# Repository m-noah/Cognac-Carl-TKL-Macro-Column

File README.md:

# Cognac-Carl-TKL-Macro-Column
 TKL with left hand macro column

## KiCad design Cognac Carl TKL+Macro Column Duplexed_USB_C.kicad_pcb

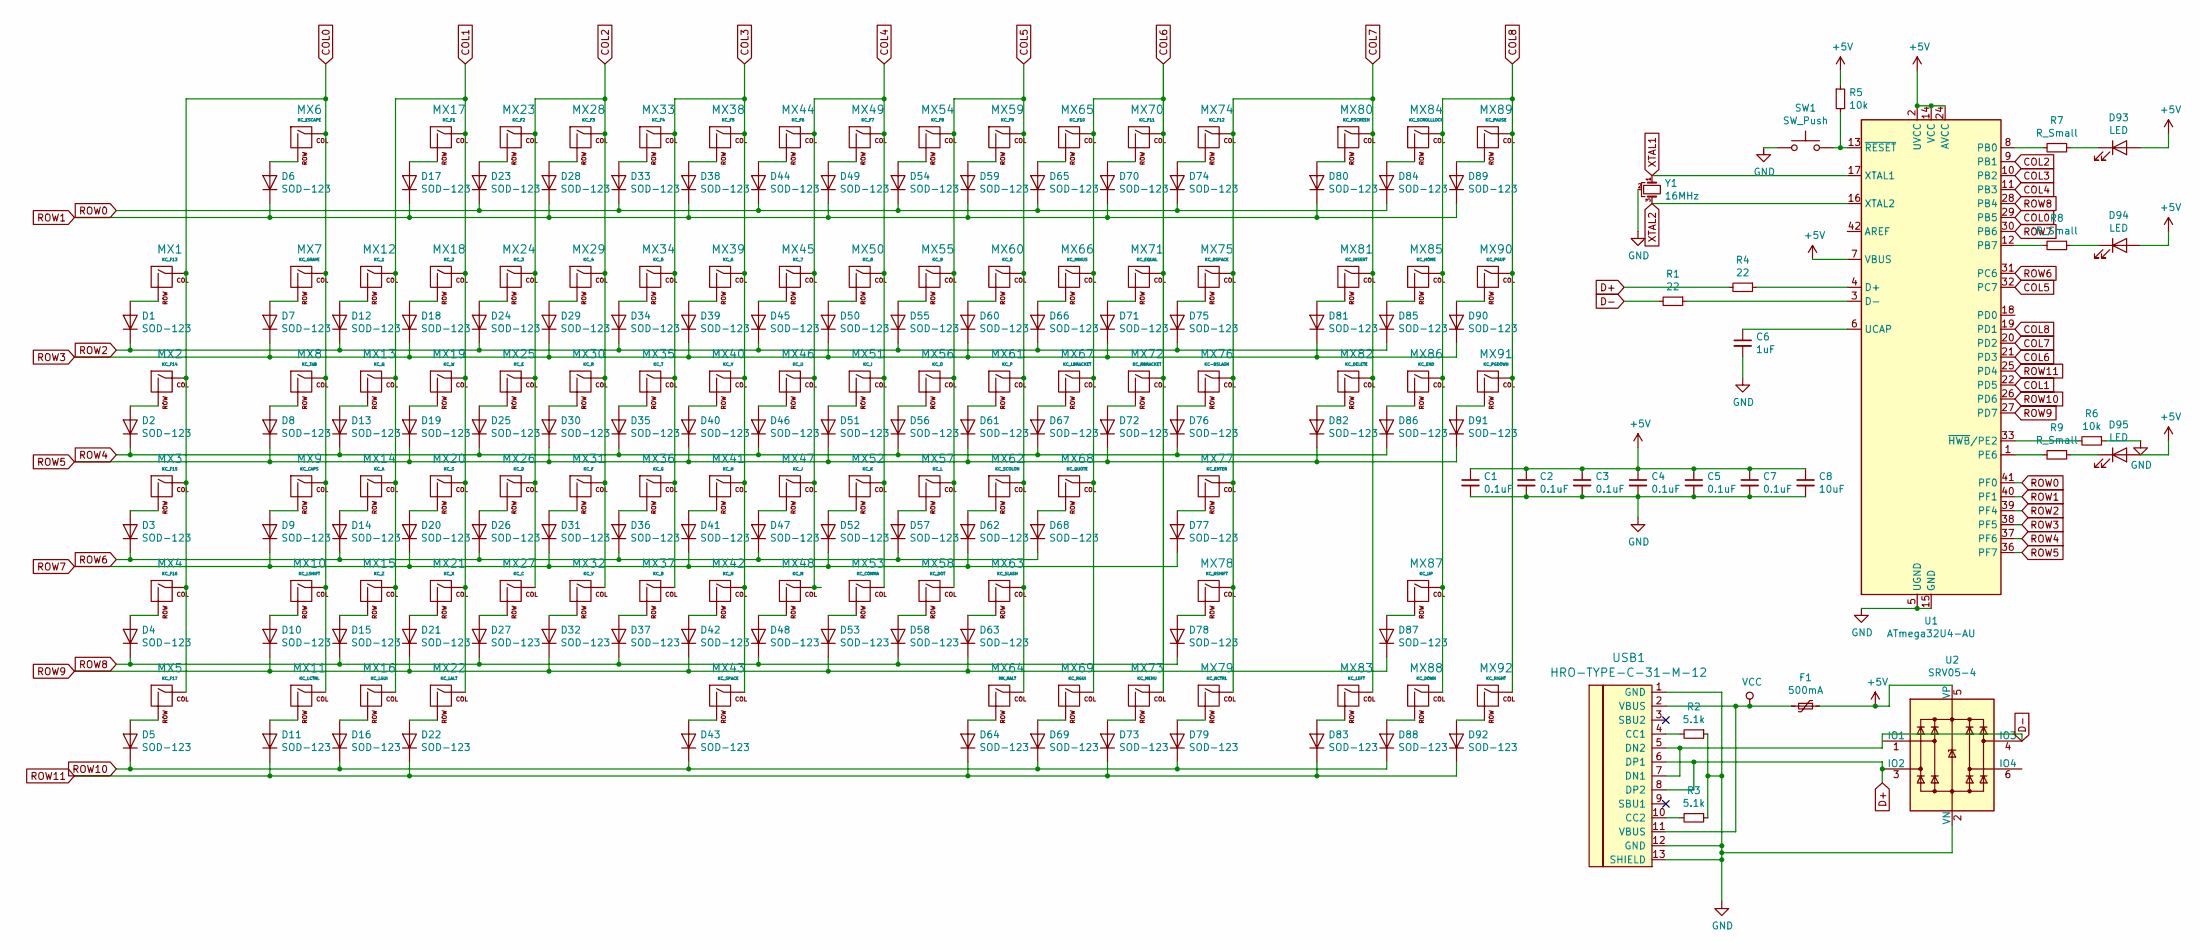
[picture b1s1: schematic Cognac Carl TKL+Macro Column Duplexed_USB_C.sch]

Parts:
C1, C2, C3, C4, C5, C7: 0.1uF; C_0805_2012Metric
C6: 1uF; C_0805_2012Metric
C8: 10uF; C_0805_2012Metric
D1, D2, D3, D4, D5, D6, D7, D8, D9, D10, D11, D12, D13, D14, D15, D16, D17, D18, D19, D20, D21, D22, D23, D24, D25, D26, D27, D28, D29, D30, D31, D32, D33, D34, D35, D36, D37, D38, D39, D40, D41, D42, D43, D44, D45, D46, D47, D48, D49, D50, D51, D52, D53, D54, D55, D56, D57, D58, D59, D60, D61, D62, D63, D64, D65, D66, D67, D68, D69, D70, D71, D72, D73, D74, D75, D76, D77, D78, D79, D80, D81, D82, D83, D84, D85, D86, D87, D88, D89, D90, D91, D92: SOD-123; D_SOD-123
D93, D94, D95: LED; LED_0805_2012Metric
F1: 500mA; Fuse_1206_3216Metric
MX1: KC_F13; MXOnly-1U-NoLED
MX2: KC_F14; MXOnly-1U-NoLED
MX3: KC_F15; MXOnly-1U-NoLED
MX4: KC_F16; MXOnly-1U-NoLED
MX5: KC_F17; MXOnly-1U-NoLED
MX6: KC_ESCAPE; MXOnly-1U-NoLED
MX7: KC_GRAVE; MXOnly-1U-NoLED
MX8: KC_TAB; MXOnly-1.5U-NoLED
MX9: KC_CAPS; MXOnly-1.75U-NoLED
MX10: KC_LSHIFT; MXOnly-2.25U-NoLED
MX11: KC_LCTRL; MXOnly-1.25U-NoLED
MX12: KC_1; MXOnly-1U-NoLED
MX13: KC_Q; MXOnly-1U-NoLED
MX14: KC_A; MXOnly-1U-NoLED
MX15: KC_Z; MXOnly-1U-NoLED
MX16: KC_LGUI; MXOnly-1.25U-NoLED
MX17: KC_F1; MXOnly-1U-NoLED
MX18: KC_2; MXOnly-1U-NoLED
MX19: KC_W; MXOnly-1U-NoLED
MX20: KC_S; MXOnly-1U-NoLED
MX21: KC_X; MXOnly-1U-NoLED
MX22: KC_LALT; MXOnly-1.25U-NoLED
MX23: KC_F2; MXOnly-1U-NoLED
MX24: KC_3; MXOnly-1U-NoLED
MX25: KC_E; MXOnly-1U-NoLED
MX26: KC_D; MXOnly-1U-NoLED
MX27: KC_C; MXOnly-1U-NoLED
MX28: KC_F3; MXOnly-1U-NoLED
MX29: KC_4; MXOnly-1U-NoLED
MX30: KC_R; MXOnly-1U-NoLED
MX31: KC_F; MXOnly-1U-NoLED
MX32: KC_V; MXOnly-1U-NoLED
MX33: KC_F4; MXOnly-1U-NoLED
MX34: KC_5; MXOnly-1U-NoLED
MX35: KC_T; MXOnly-1U-NoLED
MX36: KC_G; MXOnly-1U-NoLED
MX37: KC_B; MXOnly-1U-NoLED
MX38: KC_F5; MXOnly-1U-NoLED
MX39: KC_6; MXOnly-1U-NoLED
MX40: KC_Y; MXOnly-1U-NoLED
MX41: KC_H; MXOnly-1U-NoLED
MX42: KC_N; MXOnly-1U-NoLED
MX43: KC_SPACE; MXOnly-6.25U-ReversedStabilizers-NoLED
MX44: KC_F6; MXOnly-1U-NoLED
MX45: KC_7; MXOnly-1U-NoLED
MX46: KC_U; MXOnly-1U-NoLED
MX47: KC_J; MXOnly-1U-NoLED
MX48: KC_M; MXOnly-1U-NoLED
MX49: KC_F7; MXOnly-1U-NoLED
MX50: KC_8; MXOnly-1U-NoLED
MX51: KC_I; MXOnly-1U-NoLED
MX52: KC_K; MXOnly-1U-NoLED
MX53: KC_COMMA; MXOnly-1U-NoLED
MX54: KC_F8; MXOnly-1U-NoLED
MX55: KC_9; MXOnly-1U-NoLED
MX56: KC_O; MXOnly-1U-NoLED
MX57: KC_L; MXOnly-1U-NoLED
MX58: KC_DOT; MXOnly-1U-NoLED
MX59: KC_F9; MXOnly-1U-NoLED
MX60: KC_0; MXOnly-1U-NoLED
MX61: KC_P; MXOnly-1U-NoLED
MX62: KC_SCOLON; MXOnly-1U-NoLED
MX63: KC_SLASH; MXOnly-1U-NoLED
MX64: MX_RALT; MXOnly-1.25U-NoLED
MX65: KC_F10; MXOnly-1U-NoLED
MX66: KC_MINUS; MXOnly-1U-NoLED
MX67: KC_LBRACKET; MXOnly-1U-NoLED
MX68: KC_QUOTE; MXOnly-1U-NoLED
MX69: KC_RGUI; MXOnly-1.25U-NoLED
MX70: KC_F11; MXOnly-1U-NoLED
MX71: KC_EQUAL; MXOnly-1U-NoLED
MX72: KC_RBRACKET; MXOnly-1U-NoLED
MX73: KC_MENU; MXOnly-1.25U-NoLED
MX74: KC_F12; MXOnly-1U-NoLED
MX75: KC_BSPACE; MXOnly-2U-NoLED
MX76: KC-BSLASH; MXOnly-1.5U-NoLED
MX77: KC_ENTER; MXOnly-2.25U-ReversedStabilizers-NoLED
MX78: KC_RSHIFT; MXOnly-2.75U-NoLED
MX79: KC_RCTRL; MXOnly-1.25U-NoLED
MX80: KC_PSCREEN; MXOnly-1U-NoLED
MX81: KC_INSERT; MXOnly-1U-NoLED
MX82: KC_DELETE; MXOnly-1U-NoLED
MX83: KC_LEFT; MXOnly-1U-NoLED
MX84: KC_SCROLLLOCK; MXOnly-1U-NoLED
MX85: KC_HOME; MXOnly-1U-NoLED
MX86: KC_END; MXOnly-1U-NoLED
MX87: KC_UP; MXOnly-1U-NoLED
MX88: KC_DOWN; MXOnly-1U-NoLED
MX89: KC_PAUSE; MXOnly-1U-NoLED
MX90: KC_PGUP; MXOnly-1U-NoLED
MX91: KC_PGDOWN; MXOnly-1U-NoLED
MX92: KC_RIGHT; MXOnly-1U-NoLED
R1, R4: 22; R_0805_2012Metric
R2, R3: 5.1k; R_0805_2012Metric
R5, R6: 10k; R_0805_2012Metric
R7, R8, R9: R_Small; R_0805_2012Metric
SW1: SW_Push; SKQG-1155865
U1: ATmega32U4-AU; TQFP-44_10x10mm_P0.8mm
U2: SRV05-4; SOT-23-6
USB1: HRO-TYPE-C-31-M-12
Y1: 16MHz; Resonator_SMD_muRata_CSTxExxV-3Pin_3.0x1.1mm

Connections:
+5V: C1.1, C2.1, C3.1, C4.1, C5.1, C7.1, C8.1, D93.2 (A), D94.2 (A), D95.2 (A), F1.1, R5.1, U1.2 (UVCC), U1.7 (VBUS), U1.14 (VCC), U1.24 (AVCC), U1.34 (VCC), U1.44 (AVCC), U2.5 (VP)
COL0: MX1.1 (COL), MX2.1 (COL), MX3.1 (COL), MX4.1 (COL), MX5.1 (COL), MX6.1 (COL), MX7.1 (COL), MX8.1 (COL), MX9.1 (COL), MX10.1 (COL), MX11.1 (COL), U1.29 (PB5)
COL1: MX12.1 (COL), MX13.1 (COL), MX14.1 (COL), MX15.1 (COL), MX16.1 (COL), MX17.1 (COL), MX18.1 (COL), MX19.1 (COL), MX20.1 (COL), MX21.1 (COL), MX22.1 (COL), U1.22 (PD5)
COL2: MX23.1 (COL), MX24.1 (COL), MX25.1 (COL), MX26.1 (COL), MX27.1 (COL), MX28.1 (COL), MX29.1 (COL), MX30.1 (COL), MX31.1 (COL), MX32.1 (COL), U1.9 (PB1)
COL3: MX33.1 (COL), MX34.1 (COL), MX35.1 (COL), MX36.1 (COL), MX37.1 (COL), MX38.1 (COL), MX39.1 (COL), MX40.1 (COL), MX41.1 (COL), MX42.1 (COL), MX43.1 (COL), U1.10 (PB2)
COL4: MX44.1 (COL), MX45.1 (COL), MX46.1 (COL), MX47.1 (COL), MX48.1 (COL), MX49.1 (COL), MX50.1 (COL), MX51.1 (COL), MX52.1 (COL), MX53.1 (COL), U1.11 (PB3)
COL5: MX54.1 (COL), MX55.1 (COL), MX56.1 (COL), MX57.1 (COL), MX58.1 (COL), MX59.1 (COL), MX60.1 (COL), MX61.1 (COL), MX62.1 (COL), MX63.1 (COL), MX64.1 (COL), U1.32 (PC7)
COL6: MX65.1 (COL), MX66.1 (COL), MX67.1 (COL), MX68.1 (COL), MX69.1 (COL), MX70.1 (COL), MX71.1 (COL), MX72.1 (COL), MX73.1 (COL), U1.21 (PD3)
COL7: MX74.1 (COL), MX75.1 (COL), MX76.1 (COL), MX77.1 (COL), MX78.1 (COL), MX79.1 (COL), MX80.1 (COL), MX81.1 (COL), MX82.1 (COL), MX83.1 (COL), U1.20 (PD2)
COL8: MX84.1 (COL), MX85.1 (COL), MX86.1 (COL), MX87.1 (COL), MX88.1 (COL), MX89.1 (COL), MX90.1 (COL), MX91.1 (COL), MX92.1 (COL), U1.19 (PD1)
D+: R4.2, U2.3 (IO2), USB1.6 (DP1), USB1.8 (DP2)
D-: R1.2, U2.4 (IO3), USB1.5 (DN2), USB1.7 (DN1)
GND: C1.2, C2.2, C3.2, C4.2, C5.2, C6.2, C7.2, C8.2, R2.1, R3.1, R6.1, SW1.1, U1.5 (UGND), U1.15 (GND), U1.23 (GND), U1.35 (GND), U1.43 (GND), U2.2 (VN), USB1.1 (GND), USB1.12 (GND), USB1.13 (SHIELD), Y1.2
unnamed: C6.1, U1.6 (UCAP)
unnamed: D1.2 (A), MX1.2 (ROW)
unnamed: D2.2 (A), MX2.2 (ROW)
unnamed: D3.2 (A), MX3.2 (ROW)
unnamed: D4.2 (A), MX4.2 (ROW)
unnamed: D5.2 (A), MX5.2 (ROW)
unnamed: D6.2 (A), MX6.2 (ROW)
unnamed: D7.2 (A), MX7.2 (ROW)
unnamed: D8.2 (A), MX8.2 (ROW)
unnamed: D9.2 (A), MX9.2 (ROW)
unnamed: D10.2 (A), MX10.2 (ROW)
unnamed: D11.2 (A), MX11.2 (ROW)
unnamed: D12.2 (A), MX12.2 (ROW)
unnamed: D13.2 (A), MX13.2 (ROW)
unnamed: D14.2 (A), MX14.2 (ROW)
unnamed: D15.2 (A), MX15.2 (ROW)
unnamed: D16.2 (A), MX16.2 (ROW)
unnamed: D17.2 (A), MX17.2 (ROW)
unnamed: D18.2 (A), MX18.2 (ROW)
unnamed: D19.2 (A), MX19.2 (ROW)
unnamed: D20.2 (A), MX20.2 (ROW)
unnamed: D21.2 (A), MX21.2 (ROW)
unnamed: D22.2 (A), MX22.2 (ROW)
unnamed: D23.2 (A), MX23.2 (ROW)
unnamed: D24.2 (A), MX24.2 (ROW)
unnamed: D25.2 (A), MX25.2 (ROW)
unnamed: D26.2 (A), MX26.2 (ROW)
unnamed: D27.2 (A), MX27.2 (ROW)
unnamed: D28.2 (A), MX28.2 (ROW)
unnamed: D29.2 (A), MX29.2 (ROW)
unnamed: D30.2 (A), MX30.2 (ROW)
unnamed: D31.2 (A), MX31.2 (ROW)
unnamed: D32.2 (A), MX32.2 (ROW)
unnamed: D33.2 (A), MX33.2 (ROW)
unnamed: D34.2 (A), MX34.2 (ROW)
unnamed: D35.2 (A), MX35.2 (ROW)
unnamed: D36.2 (A), MX36.2 (ROW)
unnamed: D37.2 (A), MX37.2 (ROW)
unnamed: D38.2 (A), MX38.2 (ROW)
unnamed: D39.2 (A), MX39.2 (ROW)
unnamed: D40.2 (A), MX40.2 (ROW)
unnamed: D41.2 (A), MX41.2 (ROW)
unnamed: D42.2 (A), MX42.2 (ROW)
unnamed: D43.2 (A), MX43.2 (ROW)
unnamed: D44.2 (A), MX44.2 (ROW)
unnamed: D45.2 (A), MX45.2 (ROW)
unnamed: D46.2 (A), MX46.2 (ROW)
unnamed: D47.2 (A), MX47.2 (ROW)
unnamed: D48.2 (A), MX48.2 (ROW)
unnamed: D49.2 (A), MX49.2 (ROW)
unnamed: D50.2 (A), MX50.2 (ROW)
unnamed: D51.2 (A), MX51.2 (ROW)
unnamed: D52.2 (A), MX52.2 (ROW)
unnamed: D53.2 (A), MX53.2 (ROW)
unnamed: D54.2 (A), MX54.2 (ROW)
unnamed: D55.2 (A), MX55.2 (ROW)
unnamed: D56.2 (A), MX56.2 (ROW)
unnamed: D57.2 (A), MX57.2 (ROW)
unnamed: D58.2 (A), MX58.2 (ROW)
unnamed: D59.2 (A), MX59.2 (ROW)
unnamed: D60.2 (A), MX60.2 (ROW)
unnamed: D61.2 (A), MX61.2 (ROW)
unnamed: D62.2 (A), MX62.2 (ROW)
unnamed: D63.2 (A), MX63.2 (ROW)
unnamed: D64.2 (A), MX64.2 (ROW)
unnamed: D65.2 (A), MX65.2 (ROW)
unnamed: D66.2 (A), MX66.2 (ROW)
unnamed: D67.2 (A), MX67.2 (ROW)
unnamed: D68.2 (A), MX68.2 (ROW)
unnamed: D69.2 (A), MX69.2 (ROW)
unnamed: D70.2 (A), MX70.2 (ROW)
unnamed: D71.2 (A), MX71.2 (ROW)
unnamed: D72.2 (A), MX72.2 (ROW)
unnamed: D73.2 (A), MX73.2 (ROW)
unnamed: D74.2 (A), MX74.2 (ROW)
unnamed: D75.2 (A), MX75.2 (ROW)
unnamed: D76.2 (A), MX76.2 (ROW)
unnamed: D77.2 (A), MX77.2 (ROW)
unnamed: D78.2 (A), MX78.2 (ROW)
unnamed: D79.2 (A), MX79.2 (ROW)
unnamed: D80.2 (A), MX80.2 (ROW)
unnamed: D81.2 (A), MX81.2 (ROW)
unnamed: D82.2 (A), MX82.2 (ROW)
unnamed: D83.2 (A), MX83.2 (ROW)
unnamed: D84.2 (A), MX84.2 (ROW)
unnamed: D85.2 (A), MX85.2 (ROW)
unnamed: D86.2 (A), MX86.2 (ROW)
unnamed: D87.2 (A), MX87.2 (ROW)
unnamed: D88.2 (A), MX88.2 (ROW)
unnamed: D89.2 (A), MX89.2 (ROW)
unnamed: D90.2 (A), MX90.2 (ROW)
unnamed: D91.2 (A), MX91.2 (ROW)
unnamed: D92.2 (A), MX92.2 (ROW)
unnamed: D93.1 (K), R7.1
unnamed: D94.1 (K), R8.1
unnamed: D95.1 (K), R9.1
unnamed: R1.1, U1.3 (D-)
unnamed: R2.2, USB1.4 (CC1)
unnamed: R3.2, USB1.10 (CC2)
unnamed: R4.1, U1.4 (D+)
unnamed: R5.2, SW1.2, U1.13 (~RESET)
unnamed: R6.2, U1.33 (~HWB~/PE2)
unnamed: R7.2, U1.8 (PB0)
unnamed: R8.2, U1.12 (PB7)
unnamed: R9.2, U1.1 (PE6)
ROW0: D23.1 (K), D33.1 (K), D44.1 (K), D54.1 (K), D65.1 (K), D74.1 (K), D84.1 (K), U1.41 (PF0)
ROW1: D6.1 (K), D17.1 (K), D28.1 (K), D38.1 (K), D49.1 (K), D59.1 (K), D70.1 (K), D80.1 (K), D89.1 (K), U1.40 (PF1)
ROW2: D1.1 (K), D12.1 (K), D24.1 (K), D34.1 (K), D45.1 (K), D55.1 (K), D66.1 (K), D75.1 (K), D85.1 (K), U1.39 (PF4)
ROW3: D7.1 (K), D18.1 (K), D29.1 (K), D39.1 (K), D50.1 (K), D60.1 (K), D71.1 (K), D81.1 (K), D90.1 (K), U1.38 (PF5)
ROW4: D2.1 (K), D13.1 (K), D25.1 (K), D35.1 (K), D46.1 (K), D56.1 (K), D67.1 (K), D76.1 (K), D86.1 (K), U1.37 (PF6)
ROW5: D8.1 (K), D19.1 (K), D30.1 (K), D40.1 (K), D51.1 (K), D61.1 (K), D72.1 (K), D82.1 (K), D91.1 (K), U1.36 (PF7)
ROW6: D3.1 (K), D14.1 (K), D26.1 (K), D36.1 (K), D47.1 (K), D57.1 (K), D68.1 (K), U1.31 (PC6)
ROW7: D9.1 (K), D20.1 (K), D31.1 (K), D41.1 (K), D52.1 (K), D62.1 (K), D77.1 (K), U1.30 (PB6)
ROW8: D4.1 (K), D15.1 (K), D27.1 (K), D37.1 (K), D48.1 (K), D58.1 (K), D78.1 (K), U1.28 (PB4)
ROW9: D10.1 (K), D21.1 (K), D32.1 (K), D42.1 (K), D53.1 (K), D63.1 (K), D87.1 (K), U1.27 (PD7)
ROW10: D5.1 (K), D16.1 (K), D43.1 (K), D69.1 (K), D79.1 (K), D88.1 (K), U1.26 (PD6)
ROW11: D11.1 (K), D22.1 (K), D64.1 (K), D73.1 (K), D83.1 (K), D92.1 (K), U1.25 (PD4)
VCC: F1.2, USB1.2 (VBUS), USB1.11 (VBUS)
XTAL1: U1.17 (XTAL1), Y1.1
XTAL2: U1.16 (XTAL2), Y1.3

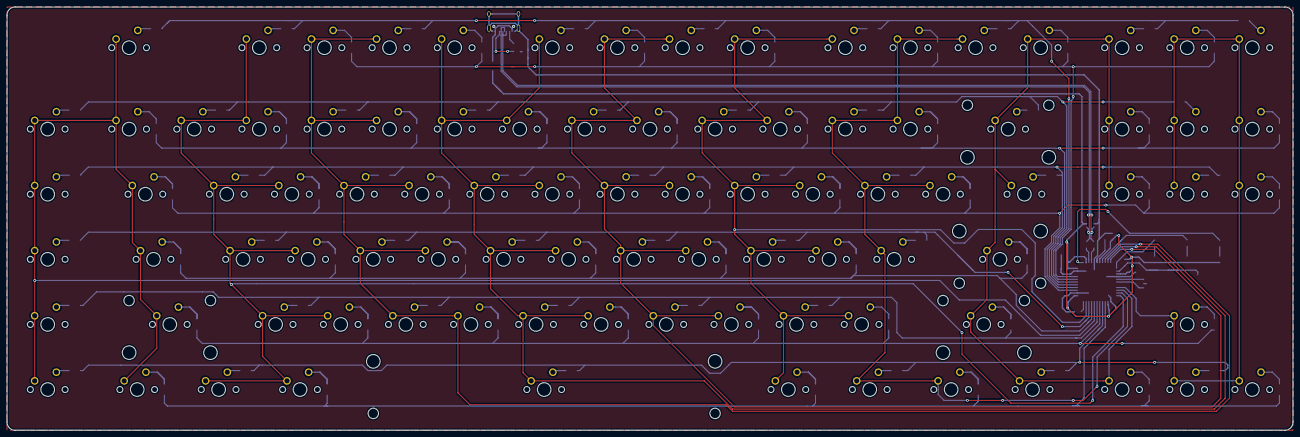
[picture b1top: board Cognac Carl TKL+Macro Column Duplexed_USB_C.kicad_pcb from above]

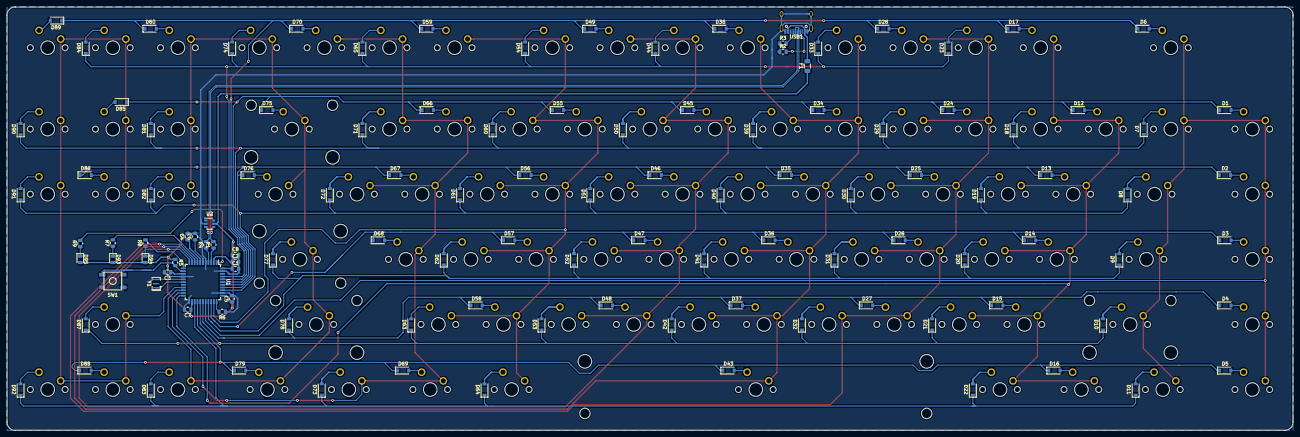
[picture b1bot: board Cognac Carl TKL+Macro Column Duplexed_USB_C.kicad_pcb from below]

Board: 2 copper layers, 376.2 x 123.8 mm, 210 parts (118 on the bottom side), 133 nets.

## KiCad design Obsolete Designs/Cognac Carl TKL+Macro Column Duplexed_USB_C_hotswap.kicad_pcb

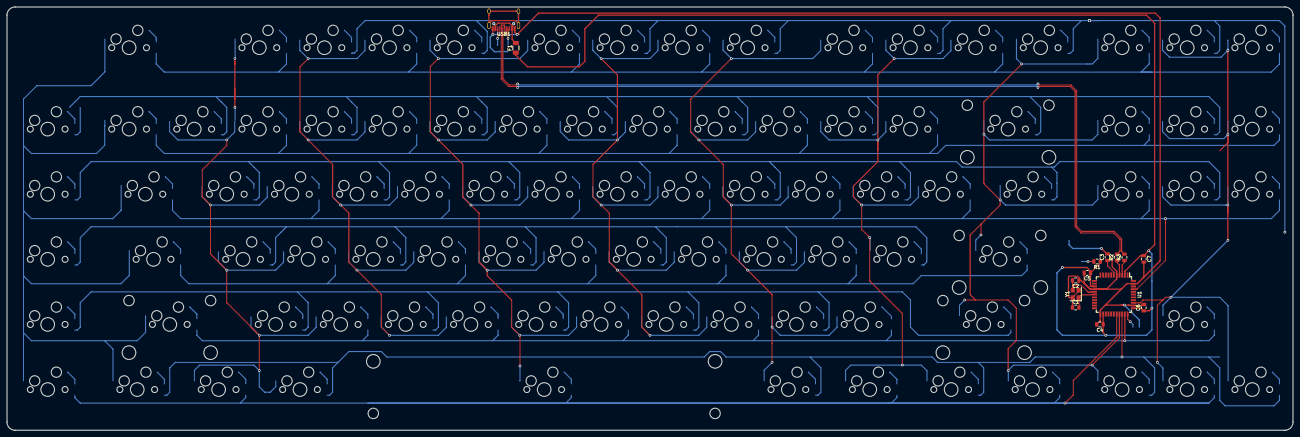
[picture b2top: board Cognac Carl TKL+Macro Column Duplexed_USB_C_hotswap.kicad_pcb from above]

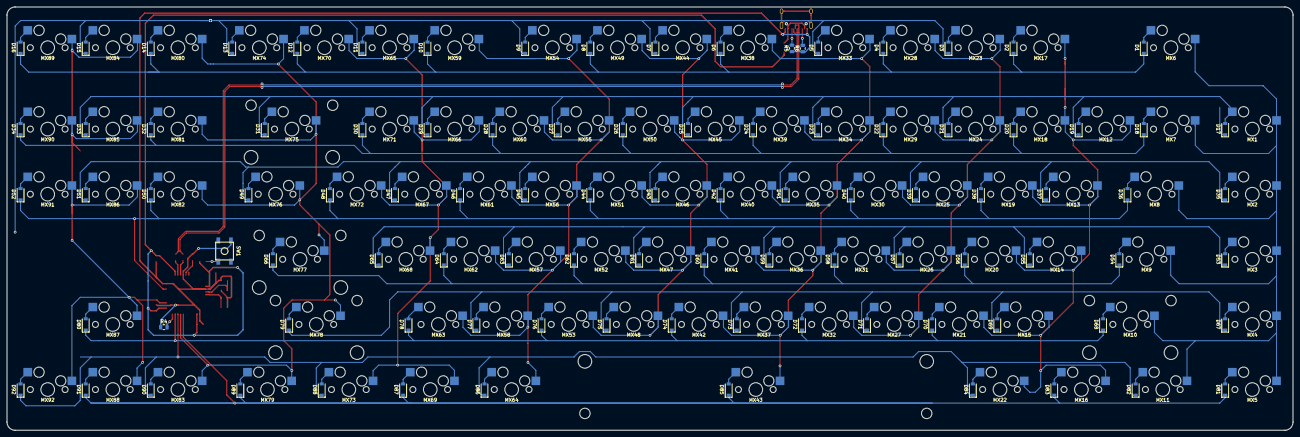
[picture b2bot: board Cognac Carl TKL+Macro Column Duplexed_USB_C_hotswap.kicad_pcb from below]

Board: 2 copper layers, 376.2 x 123.8 mm, 202 parts (96 on the bottom side), 127 nets.

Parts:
C1, C2: 22pF; C_0805_2012Metric
C3: 1uF; C_0805_2012Metric
C4, C5, C6: 0.1uF; C_0805_2012Metric
C7: 10uF; C_0805_2012Metric
D1, D2, D3, D4, D5, D6, D7, D8, D9, D10, D11, D12, D13, D14, D15, D16, D17, D18, D19, D20, D21, D22, D23, D24, D25, D26, D27, D28, D29, D30, D31, D32, D33, D34, D35, D36, D37, D38, D39, D40, D41, D42, D43, D44, D45, D46, D47, D48, D49, D50, D51, D52, D53, D54, D55, D56, D57, D58, D59, D60, D61, D62, D63, D64, D65, D66, D67, D68, D69, D70, D71, D72, D73, D74, D75, D76, D77, D78, D79, D80, D81, D82, D83, D84, D85, D86, D87, D88, D89, D90, D91, D92: SOD-123; D_SOD-123
F1: 500mA; Fuse_1206_3216Metric
MX1: KC_F13; MXOnly-1U-Hotswap
MX2: KC_F14; MXOnly-1U-Hotswap
MX3: KC_F15; MXOnly-1U-Hotswap
MX4: KC_F16; MXOnly-1U-Hotswap
MX5: KC_F17; MXOnly-1U-Hotswap
MX6: KC_ESCAPE; MXOnly-1U-Hotswap
MX7: KC_GRAVE; MXOnly-1U-Hotswap
MX8: KC_TAB; MXOnly-1.5U-Hotswap
MX9: KC_CAPS; MXOnly-1.75U-Hotswap
MX10: KC_LSHIFT; MXOnly-2.25U-Hotswap
MX11: KC_LCTRL; MXOnly-1.25U-Hotswap
MX12: KC_1; MXOnly-1U-Hotswap
MX13: KC_Q; MXOnly-1U-Hotswap
MX14: KC_A; MXOnly-1U-Hotswap
MX15: KC_Z; MXOnly-1U-Hotswap
MX16: KC_LGUI; MXOnly-1.25U-Hotswap
MX17: KC_F1; MXOnly-1U-Hotswap
MX18: KC_2; MXOnly-1U-Hotswap
MX19: KC_W; MXOnly-1U-Hotswap
MX20: KC_S; MXOnly-1U-Hotswap
MX21: KC_X; MXOnly-1U-Hotswap
MX22: KC_LALT; MXOnly-1.25U-Hotswap
MX23: KC_F2; MXOnly-1U-Hotswap
MX24: KC_3; MXOnly-1U-Hotswap
MX25: KC_E; MXOnly-1U-Hotswap
MX26: KC_D; MXOnly-1U-Hotswap
MX27: KC_C; MXOnly-1U-Hotswap
MX28: KC_F3; MXOnly-1U-Hotswap
MX29: KC_4; MXOnly-1U-Hotswap
MX30: KC_R; MXOnly-1U-Hotswap
MX31: KC_F; MXOnly-1U-Hotswap
MX32: KC_V; MXOnly-1U-Hotswap
MX33: KC_F4; MXOnly-1U-Hotswap
MX34: KC_5; MXOnly-1U-Hotswap
MX35: KC_T; MXOnly-1U-Hotswap
MX36: KC_G; MXOnly-1U-Hotswap
MX37: KC_B; MXOnly-1U-Hotswap
MX38: KC_F5; MXOnly-1U-Hotswap
MX39: KC_6; MXOnly-1U-Hotswap
MX40: KC_Y; MXOnly-1U-Hotswap
MX41: KC_H; MXOnly-1U-Hotswap
MX42: KC_N; MXOnly-1U-Hotswap
MX43: KC_SPACE; MXOnly-6.25U-Hotswap-ReversedStabilizers
MX44: KC_F6; MXOnly-1U-Hotswap
MX45: KC_7; MXOnly-1U-Hotswap
MX46: KC_U; MXOnly-1U-Hotswap
MX47: KC_J; MXOnly-1U-Hotswap
MX48: KC_M; MXOnly-1U-Hotswap
MX49: KC_F7; MXOnly-1U-Hotswap
MX50: KC_8; MXOnly-1U-Hotswap
MX51: KC_I; MXOnly-1U-Hotswap
MX52: KC_K; MXOnly-1U-Hotswap
MX53: KC_COMMA; MXOnly-1U-Hotswap
MX54: KC_F8; MXOnly-1U-Hotswap
MX55: KC_9; MXOnly-1U-Hotswap
MX56: KC_O; MXOnly-1U-Hotswap
MX57: KC_L; MXOnly-1U-Hotswap
MX58: KC_DOT; MXOnly-1U-Hotswap
MX59: KC_F9; MXOnly-1U-Hotswap
MX60: KC_0; MXOnly-1U-Hotswap
MX61: KC_P; MXOnly-1U-Hotswap
MX62: KC_SCOLON; MXOnly-1U-Hotswap
MX63: KC_SLASH; MXOnly-1U-Hotswap
MX64: MX_RALT; MXOnly-1.25U-Hotswap
MX65: KC_F10; MXOnly-1U-Hotswap
MX66: KC_MINUS; MXOnly-1U-Hotswap
MX67: KC_LBRACKET; MXOnly-1U-Hotswap
MX68: KC_QUOTE; MXOnly-1U-Hotswap
MX69: KC_RGUI; MXOnly-1.25U-Hotswap
MX70: KC_F11; MXOnly-1U-Hotswap
MX71: KC_EQUAL; MXOnly-1U-Hotswap
MX72: KC_RBRACKET; MXOnly-1U-Hotswap
MX73: KC_MENU; MXOnly-1.25U-Hotswap
MX74: KC_F12; MXOnly-1U-Hotswap
MX75: KC_BSPACE; MXOnly-2U-Hotswap
MX76: KC-BSLASH; MXOnly-1.5U-Hotswap
MX77: KC_ENTER; MXOnly-2.25U-Hotswap
MX78: KC_RSHIFT; MXOnly-2.75U-Hotswap
MX79: KC_RCTRL; MXOnly-1.25U-Hotswap
MX80: KC_PSCREEN; MXOnly-1U-Hotswap
MX81: KC_INSERT; MXOnly-1U-Hotswap
MX82: KC_DELETE; MXOnly-1U-Hotswap
MX83: KC_LEFT; MXOnly-1U-Hotswap
MX84: KC_SCROLLLOCK; MXOnly-1U-Hotswap
MX85: KC_HOME; MXOnly-1U-Hotswap
MX86: KC_END; MXOnly-1U-Hotswap
MX87: KC_UP; MXOnly-1U-Hotswap
MX88: KC_DOWN; MXOnly-1U-Hotswap
MX89: KC_PAUSE; MXOnly-1U-Hotswap
MX90: KC_PGUP; MXOnly-1U-Hotswap
MX91: KC_PGDOWN; MXOnly-1U-Hotswap
MX92: KC_RIGHT; MXOnly-1U-Hotswap
R1, R4: 10k; R_0805_2012Metric
R2, R3: 22; R_0805_2012Metric
R5, R6: 5.1k; R_0805_2012Metric
SW1: SW_Push; SKQG-1155865
U1: ATmega32U4-AU; TQFP-44_10x10mm_P0.8mm
USB1: HRO-TYPE-C-31-M-12
Y1: 16MHz; Crystal_SMD_3225-4Pin_3.2x2.5mm

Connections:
+5V: C4.1, C5.1, C6.1, C7.1, F1.1, R1.1, U1.2, U1.7, U1.14, U1.24, U1.34, U1.44
COL0: MX1.1, MX2.1, MX3.1, MX4.1, MX5.1, MX6.1, MX7.1, MX8.1, MX9.1, MX10.1, MX11.1
COL1: MX12.1, MX13.1, MX14.1, MX15.1, MX16.1, MX17.1, MX18.1, MX19.1, MX20.1, MX21.1, MX22.1
COL2: MX23.1, MX24.1, MX25.1, MX26.1, MX27.1, MX28.1, MX29.1, MX30.1, MX31.1, MX32.1
COL3: MX33.1, MX34.1, MX35.1, MX36.1, MX37.1, MX38.1, MX39.1, MX40.1, MX41.1, MX42.1, MX43.1
COL4: MX44.1, MX45.1, MX46.1, MX47.1, MX48.1, MX49.1, MX50.1, MX51.1, MX52.1, MX53.1
COL5: MX54.1, MX55.1, MX56.1, MX57.1, MX58.1, MX59.1, MX60.1, MX61.1, MX62.1, MX63.1, MX64.1
COL6: MX65.1, MX66.1, MX67.1, MX68.1, MX69.1, MX70.1, MX71.1, MX72.1, MX73.1
COL7: MX74.1, MX75.1, MX76.1, MX77.1, MX78.1, MX79.1, MX80.1, MX81.1, MX82.1, MX83.1, U1.30
COL8: MX84.1, MX85.1, MX86.1, MX87.1, MX88.1, MX89.1, MX90.1, MX91.1, MX92.1, U1.36
D+: R2.2, USB1.6, USB1.8
D-: R3.2, USB1.5, USB1.7
GND: C1.1, C2.1, C3.2, C4.2, C5.2, C6.2, C7.2, R4.1, R5.1, R6.1, SW1.1, U1.5, U1.15, U1.23, U1.35, U1.43, USB1.1, USB1.12, USB1.13, Y1.2, Y1.4
unnamed: C1.2, U1.17, Y1.1
unnamed: C2.2, U1.16, Y1.3
unnamed: C3.1, U1.6
unnamed: D1.2, MX6.2
unnamed: D2.2, MX17.2
unnamed: D3.2, MX23.2
unnamed: D4.2, MX28.2
unnamed: D5.2, MX33.2
unnamed: D6.2, MX38.2
unnamed: D7.2, MX44.2
unnamed: D8.2, MX49.2
unnamed: D9.2, MX54.2
unnamed: D10.2, MX59.2
unnamed: D11.2, MX65.2
unnamed: D12.2, MX70.2
unnamed: D13.2, MX74.2
unnamed: D14.2, MX80.2
unnamed: D15.2, MX84.2
unnamed: D16.2, MX89.2
unnamed: D17.2, MX1.2
unnamed: D18.2, MX7.2
unnamed: D19.2, MX12.2
unnamed: D20.2, MX18.2
unnamed: D21.2, MX24.2
unnamed: D22.2, MX29.2
unnamed: D23.2, MX34.2
unnamed: D24.2, MX39.2
unnamed: D25.2, MX45.2
unnamed: D26.2, MX50.2
unnamed: D27.2, MX55.2
unnamed: D28.2, MX60.2
unnamed: D29.2, MX66.2
unnamed: D30.2, MX71.2
unnamed: D31.2, MX75.2
unnamed: D32.2, MX81.2
unnamed: D33.2, MX85.2
unnamed: D34.2, MX90.2
unnamed: D35.2, MX2.2
unnamed: D36.2, MX8.2
unnamed: D37.2, MX13.2
unnamed: D38.2, MX19.2
unnamed: D39.2, MX25.2
unnamed: D40.2, MX30.2
unnamed: D41.2, MX35.2
unnamed: D42.2, MX40.2
unnamed: D43.2, MX46.2
unnamed: D44.2, MX51.2
unnamed: D45.2, MX56.2
unnamed: D46.2, MX61.2
unnamed: D47.2, MX67.2
unnamed: D48.2, MX72.2
unnamed: D49.2, MX76.2
unnamed: D50.2, MX82.2
unnamed: D51.2, MX86.2
unnamed: D52.2, MX91.2
unnamed: D53.2, MX3.2
unnamed: D54.2, MX9.2
unnamed: D55.2, MX14.2
unnamed: D56.2, MX20.2
unnamed: D57.2, MX26.2
unnamed: D58.2, MX31.2
unnamed: D59.2, MX36.2
unnamed: D60.2, MX41.2
unnamed: D61.2, MX47.2
unnamed: D62.2, MX52.2
unnamed: D63.2, MX57.2
unnamed: D64.2, MX62.2
unnamed: D65.2, MX68.2
unnamed: D66.2, MX77.2
unnamed: D67.2, MX4.2
unnamed: D68.2, MX10.2
unnamed: D69.2, MX15.2
unnamed: D70.2, MX21.2
unnamed: D71.2, MX27.2
unnamed: D72.2, MX32.2
unnamed: D73.2, MX37.2
unnamed: D74.2, MX42.2
unnamed: D75.2, MX48.2
unnamed: D76.2, MX53.2
unnamed: D77.2, MX58.2
unnamed: D78.2, MX63.2
unnamed: D79.2, MX78.2
unnamed: D80.2, MX87.2
unnamed: D81.2, MX5.2
unnamed: D82.2, MX11.2
unnamed: D83.2, MX16.2
unnamed: D84.2, MX22.2
unnamed: D85.2, MX43.2
unnamed: D86.2, MX64.2
unnamed: D87.2, MX69.2
unnamed: D88.2, MX73.2
unnamed: D89.2, MX79.2
unnamed: D90.2, MX83.2
unnamed: D91.2, MX88.2
unnamed: D92.2, MX92.2
unnamed: R1.2, SW1.2, U1.13
unnamed: R2.1, U1.4
unnamed: R3.1, U1.3
unnamed: R4.2, U1.33
unnamed: R5.2, USB1.4
unnamed: R6.2, USB1.10
ROW0: D3.1, D5.1, D7.1, D9.1, D11.1, D13.1, D15.1
ROW1: D1.1, D2.1, D4.1, D6.1, D8.1, D10.1, D12.1, D14.1, D16.1
ROW2: D17.1, D19.1, D21.1, D23.1, D25.1, D27.1, D29.1, D31.1, D33.1
ROW3: D18.1, D20.1, D22.1, D24.1, D26.1, D28.1, D30.1, D32.1, D34.1
ROW4: D35.1, D37.1, D39.1, D41.1, D43.1, D45.1, D47.1, D49.1, D51.1
ROW5: D36.1, D38.1, D40.1, D42.1, D44.1, D46.1, D48.1, D50.1, D52.1, U1.41
ROW6: D53.1, D55.1, D57.1, D59.1, D61.1, D63.1, D65.1
ROW7: D54.1, D56.1, D58.1, D60.1, D62.1, D64.1, D66.1
ROW8: D67.1, D69.1, D71.1, D73.1, D75.1, D77.1, D79.1
ROW9: D68.1, D70.1, D72.1, D74.1, D76.1, D78.1, D80.1, U1.32
ROW10: D81.1, D83.1, D85.1, D87.1, D89.1, D91.1, U1.29
ROW11: D82.1, D84.1, D86.1, D88.1, D90.1, D92.1, U1.31
VCC: F1.2, USB1.2, USB1.11

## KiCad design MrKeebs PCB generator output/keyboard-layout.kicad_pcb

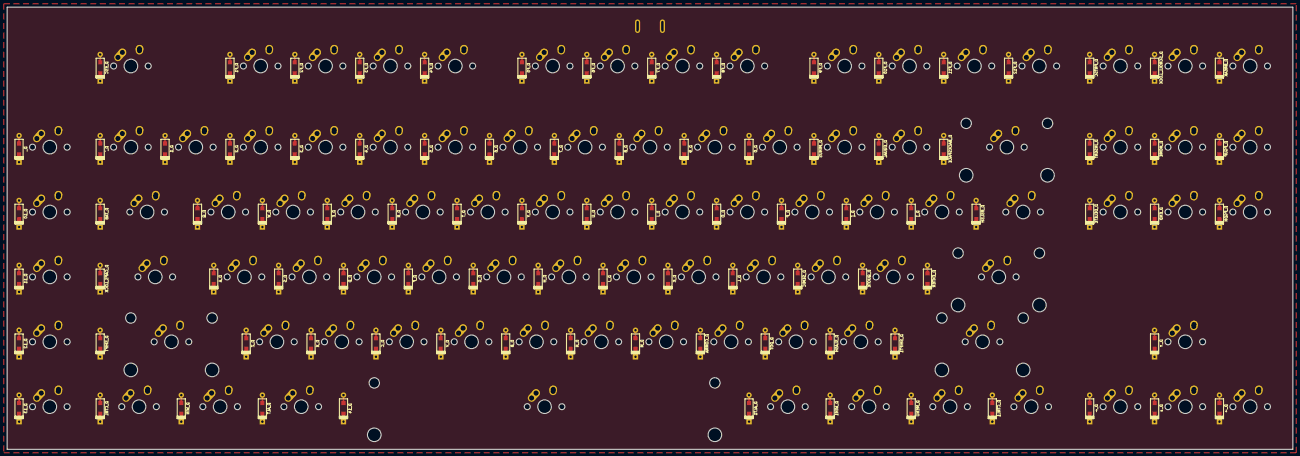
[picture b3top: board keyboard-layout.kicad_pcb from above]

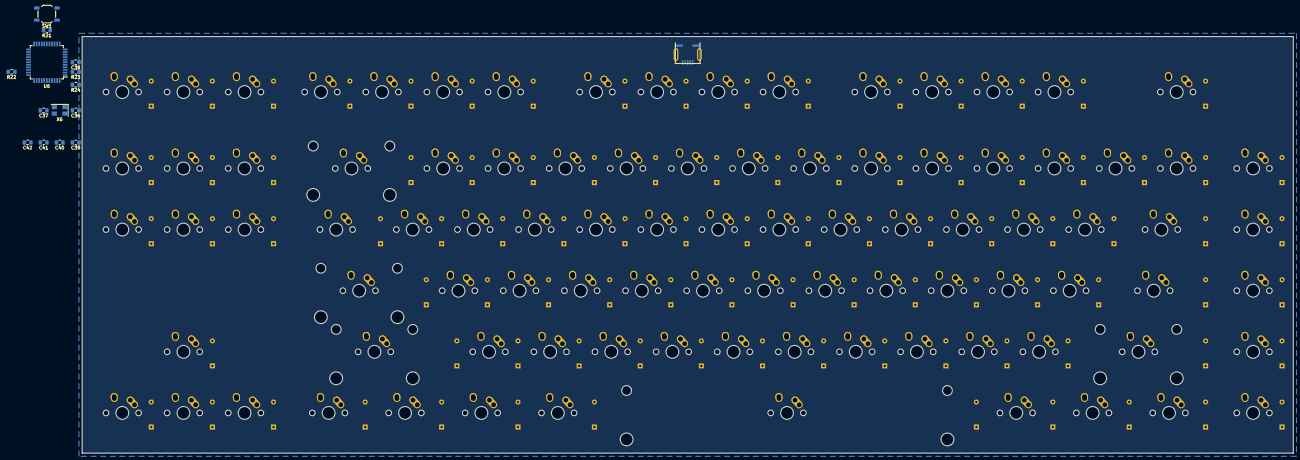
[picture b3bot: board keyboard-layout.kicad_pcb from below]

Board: 2 copper layers, 377.5 x 129.8 mm, 199 parts (15 on the bottom side), 121 nets, no tracks yet.

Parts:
C36, C37, C38, C39, C40, C41, C42: 22pF; C_0805_2012Metric_Pad1.15x1.40mm_HandSolder
D_, D_0, D_1, D_2, D_3, D_4, D_5, D_6, D_7, D_8, D_9, D_10, D_11, D_12, D_13, D_14: D; D_SOD123_axial
D_A: D; D_SOD123_axial
D_ALT, D_ALT1: D; D_SOD123_axial
D_B: D; D_SOD123_axial
D_BACKSPACE: D; D_SOD123_axial
D_BREAK: D; D_SOD123_axial
D_BSLSH: D; D_SOD123_axial
D_C: D; D_SOD123_axial
D_CAPS_LOCK: D; D_SOD123_axial
D_COMMA: D; D_SOD123_axial
D_CTRL, D_CTRL1: D; D_SOD123_axial
D_D: D; D_SOD123_axial
D_DELETE: D; D_SOD123_axial
D_DOT: D; D_SOD123_axial
D_E: D; D_SOD123_axial
D_END: D; D_SOD123_axial
D_ENTER: D; D_SOD123_axial
D_EQUAL: D; D_SOD123_axial
D_ESC: D; D_SOD123_axial
D_F, D_F1, D_F2, D_F3, D_F4, D_F5, D_F6, D_F7, D_F8, D_F9, D_F10, D_F11, D_F12: D; D_SOD123_axial
D_G: D; D_SOD123_axial
D_H: D; D_SOD123_axial
D_HOME: D; D_SOD123_axial
D_I: D; D_SOD123_axial
D_INSERT: D; D_SOD123_axial
D_J: D; D_SOD123_axial
D_K: D; D_SOD123_axial
D_L: D; D_SOD123_axial
D_M: D; D_SOD123_axial
D_MENU: D; D_SOD123_axial
D_MINUS: D; D_SOD123_axial
D_N: D; D_SOD123_axial
D_O: D; D_SOD123_axial
D_P: D; D_SOD123_axial
D_PGDN: D; D_SOD123_axial
D_PGUP: D; D_SOD123_axial
D_PRTSC: D; D_SOD123_axial
D_Q: D; D_SOD123_axial
D_QUOTE: D; D_SOD123_axial
D_R: D; D_SOD123_axial
D_S: D; D_SOD123_axial
D_SCROLL_LOCK: D; D_SOD123_axial
D_SEMIC: D; D_SOD123_axial
D_SHIFT, D_SHIFT1: D; D_SOD123_axial
D_SLASH: D; D_SOD123_axial
D_T: D; D_SOD123_axial
D_TAB: D; D_SOD123_axial
D_U: D; D_SOD123_axial
D_V: D; D_SOD123_axial
D_W: D; D_SOD123_axial
D_WIN, D_WIN1: D; D_SOD123_axial
D_X: D; D_SOD123_axial
D_Y: D; D_SOD123_axial
D_Z: D; D_SOD123_axial
D_[: D; D_SOD123_axial
D_]: D; D_SOD123_axial
D_`: D; D_SOD123_axial
D_←: D; D_SOD123_axial
D_↑: D; D_SOD123_axial
D_→: D; D_SOD123_axial
D_↓: D; D_SOD123_axial
K_, K_0, K_1, K_2, K_3, K_4, K_5, K_6, K_7, K_8, K_9, K_10, K_11, K_12, K_13: KEYSW; MX-1U-NoLED
K_14: KEYSW; MX-6.25U-NoLED
K_A: KEYSW; MX-1U-NoLED
K_ALT, K_ALT1: KEYSW; MX-1.25U-NoLED
K_B: KEYSW; MX-1U-NoLED
K_BACKSPACE: KEYSW; MX-2U-NoLED
K_BREAK: KEYSW; MX-1U-NoLED
K_BSLSH: KEYSW; MX-1.5U-NoLED
K_C: KEYSW; MX-1U-NoLED
K_CAPS_LOCK: KEYSW; MX-1.75U-NoLED
K_COMMA: KEYSW; MX-1U-NoLED
K_CTRL, K_CTRL1: KEYSW; MX-1.25U-NoLED
K_D: KEYSW; MX-1U-NoLED
K_DELETE: KEYSW; MX-1U-NoLED
K_DOT: KEYSW; MX-1U-NoLED
K_E: KEYSW; MX-1U-NoLED
K_END: KEYSW; MX-1U-NoLED
K_ENTER: KEYSW; MX-2.25U-NoLED
K_EQUAL: KEYSW; MX-1U-NoLED
K_ESC: KEYSW; MX-1U-NoLED
K_F, K_F1, K_F2, K_F3, K_F4, K_F5, K_F6, K_F7, K_F8, K_F9, K_F10, K_F11, K_F12: KEYSW; MX-1U-NoLED
K_G: KEYSW; MX-1U-NoLED
K_H: KEYSW; MX-1U-NoLED
K_HOME: KEYSW; MX-1U-NoLED
K_I: KEYSW; MX-1U-NoLED
K_INSERT: KEYSW; MX-1U-NoLED
K_J: KEYSW; MX-1U-NoLED
K_K: KEYSW; MX-1U-NoLED
K_L: KEYSW; MX-1U-NoLED
K_M: KEYSW; MX-1U-NoLED
K_MENU: KEYSW; MX-1.25U-NoLED
K_MINUS: KEYSW; MX-1U-NoLED
K_N: KEYSW; MX-1U-NoLED
K_O: KEYSW; MX-1U-NoLED
K_P: KEYSW; MX-1U-NoLED
K_PGDN: KEYSW; MX-1U-NoLED
K_PGUP: KEYSW; MX-1U-NoLED
K_PRTSC: KEYSW; MX-1U-NoLED
K_Q: KEYSW; MX-1U-NoLED
K_QUOTE: KEYSW; MX-1U-NoLED
K_R: KEYSW; MX-1U-NoLED
K_S: KEYSW; MX-1U-NoLED
K_SCROLL_LOCK: KEYSW; MX-1U-NoLED
K_SEMIC: KEYSW; MX-1U-NoLED
K_SHIFT: KEYSW; MX-2.25U-NoLED
K_SHIFT1: KEYSW; MX-2.75U-NoLED
K_SLASH: KEYSW; MX-1U-NoLED
K_T: KEYSW; MX-1U-NoLED
K_TAB: KEYSW; MX-1.5U-NoLED
K_U: KEYSW; MX-1U-NoLED
K_V: KEYSW; MX-1U-NoLED
K_W: KEYSW; MX-1U-NoLED
K_WIN, K_WIN1: KEYSW; MX-1.25U-NoLED
K_X: KEYSW; MX-1U-NoLED
K_Y: KEYSW; MX-1U-NoLED
K_Z: KEYSW; MX-1U-NoLED
K_[: KEYSW; MX-1U-NoLED
K_]: KEYSW; MX-1U-NoLED
K_`: KEYSW; MX-1U-NoLED
K_←: KEYSW; MX-1U-NoLED
K_↑: KEYSW; MX-1U-NoLED
K_→: KEYSW; MX-1U-NoLED
K_↓: KEYSW; MX-1U-NoLED
R21, R22: 10k; R_0805_2012Metric_Pad1.15x1.40mm_HandSolder
R23, R24: 22u; R_0805_2012Metric_Pad1.15x1.40mm_HandSolder
SW1: SW_PUSH; SW_SPST_TL3342
U6: ATMEGA32U4; TQFP-44_10x10mm_P0.8mm
USB6: USB_mini_micro_B; USB_miniB_hirose_5S8
X6: XTAL_GND; Crystal_SMD_5032-4Pin_5.0x3.2mm

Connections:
/col0: D_.1, D_10.1, D_11.1, D_12.1, D_13.1, D_ESC.1, U6.32
/col1: D_CAPS_LOCK.1, D_CTRL.1, D_F1.1, D_SHIFT.1, D_TAB.1, D_`.1, U6.31
/col2: D_1.1, D_A.1, D_F2.1, D_Q.1, D_WIN.1, D_Z.1, U6.12
/col3: D_2.1, D_ALT.1, D_F3.1, D_S.1, D_W.1, D_X.1, U6.30
/col4: D_3.1, D_14.1, D_C.1, D_D.1, D_E.1, D_F4.1, U6.29
/col5: D_4.1, D_ALT1.1, D_F.1, D_F5.1, D_R.1, D_V.1, U6.28
/col6: D_5.1, D_B.1, D_F6.1, D_G.1, D_T.1, D_WIN1.1, U6.11
/col7: D_6.1, D_F7.1, D_H.1, D_MENU.1, D_N.1, D_Y.1, U6.10
/col8: D_7.1, D_CTRL1.1, D_F8.1, D_J.1, D_M.1, D_U.1, U6.9
/col9: D_8.1, D_COMMA.1, D_F9.1, D_I.1, D_K.1, D_←.1, U6.8
/col10: D_9.1, D_DOT.1, D_F10.1, D_L.1, D_O.1, D_↓.1, U6.37
/col11: D_0.1, D_F11.1, D_P.1, D_SEMIC.1, D_SLASH.1, D_→.1, U6.38
/col12: D_F12.1, D_MINUS.1, D_QUOTE.1, D_SHIFT1.1, D_[.1, U6.39
/col13: D_ENTER.1, D_EQUAL.1, D_PRTSC.1, D_].1, D_↑.1, U6.40
/col14: D_BACKSPACE.1, D_BSLSH.1, D_SCROLL_LOCK.1, U6.41
/col15: D_BREAK.1, D_DELETE.1, D_INSERT.1
/col16: D_END.1, D_HOME.1
/col17: D_PGDN.1, D_PGUP.1
GND: C36.2, C37.2, C38.2, C39.2, C40.2, C41.2, C42.2, R22.2, SW1.1, U6.5, U6.15, U6.23, USB6.5, USB6.6, X6.3
unnamed: C36.1, U6.16
unnamed: C37.1, U6.17
unnamed: C38.1, U6.6
unnamed: D_0.2, K_0.2
unnamed: D_1.2, K_1.2
unnamed: D_2.2, K_2.2
unnamed: D_3.2, K_3.2
unnamed: D_4.2, K_4.2
unnamed: D_5.2, K_5.2
unnamed: D_6.2, K_6.2
unnamed: D_7.2, K_7.2
unnamed: D_8.2, K_8.2
unnamed: D_9.2, K_9.2
unnamed: D_10.2, K_10.2
unnamed: D_11.2, K_11.2
unnamed: D_12.2, K_12.2
unnamed: D_13.2, K_13.2
unnamed: D_14.2, K_14.2
unnamed: D_.2, K_.2
unnamed: D_A.2, K_A.2
unnamed: D_ALT1.2, K_ALT1.2
unnamed: D_ALT.2, K_ALT.2
unnamed: D_B.2, K_B.2
unnamed: D_BACKSPACE.2, K_BACKSPACE.2
unnamed: D_BREAK.2, K_BREAK.2
unnamed: D_BSLSH.2, K_BSLSH.2
unnamed: D_C.2, K_C.2
unnamed: D_CAPS_LOCK.2, K_CAPS_LOCK.2
unnamed: D_COMMA.2, K_COMMA.2
unnamed: D_CTRL1.2, K_CTRL1.2
unnamed: D_CTRL.2, K_CTRL.2
unnamed: D_D.2, K_D.2
unnamed: D_DELETE.2, K_DELETE.2
unnamed: D_DOT.2, K_DOT.2
unnamed: D_E.2, K_E.2
unnamed: D_END.2, K_END.2
unnamed: D_ENTER.2, K_ENTER.2
unnamed: D_EQUAL.2, K_EQUAL.2
unnamed: D_ESC.2, K_ESC.2
unnamed: D_F1.2, K_F1.2
unnamed: D_F2.2, K_F2.2
unnamed: D_F3.2, K_F3.2
unnamed: D_F4.2, K_F4.2
unnamed: D_F5.2, K_F5.2
unnamed: D_F6.2, K_F6.2
unnamed: D_F7.2, K_F7.2
unnamed: D_F8.2, K_F8.2
unnamed: D_F9.2, K_F9.2
unnamed: D_F10.2, K_F10.2
unnamed: D_F11.2, K_F11.2
unnamed: D_F12.2, K_F12.2
unnamed: D_F.2, K_F.2
unnamed: D_G.2, K_G.2
unnamed: D_H.2, K_H.2
unnamed: D_HOME.2, K_HOME.2
unnamed: D_I.2, K_I.2
unnamed: D_INSERT.2, K_INSERT.2
unnamed: D_J.2, K_J.2
unnamed: D_K.2, K_K.2
unnamed: D_L.2, K_L.2
unnamed: D_M.2, K_M.2
unnamed: D_MENU.2, K_MENU.2
unnamed: D_MINUS.2, K_MINUS.2
unnamed: D_N.2, K_N.2
unnamed: D_O.2, K_O.2
unnamed: D_P.2, K_P.2
unnamed: D_PGDN.2, K_PGDN.2
unnamed: D_PGUP.2, K_PGUP.2
unnamed: D_PRTSC.2, K_PRTSC.2
unnamed: D_Q.2, K_Q.2
unnamed: D_QUOTE.2, K_QUOTE.2
unnamed: D_R.2, K_R.2
unnamed: D_S.2, K_S.2
unnamed: D_SCROLL_LOCK.2, K_SCROLL_LOCK.2
unnamed: D_SEMIC.2, K_SEMIC.2
unnamed: D_SHIFT1.2, K_SHIFT1.2
unnamed: D_SHIFT.2, K_SHIFT.2
unnamed: D_SLASH.2, K_SLASH.2
unnamed: D_T.2, K_T.2
unnamed: D_TAB.2, K_TAB.2
unnamed: D_U.2, K_U.2
unnamed: D_V.2, K_V.2
unnamed: D_W.2, K_W.2
unnamed: D_WIN1.2, K_WIN1.2
unnamed: D_WIN.2, K_WIN.2
unnamed: D_X.2, K_X.2
unnamed: D_Y.2, K_Y.2
unnamed: D_Z.2, K_Z.2
unnamed: D_[.2, K_[.2
unnamed: D_].2, K_].2
unnamed: D_`.2, K_`.2
unnamed: D_←.2, K_←.2
unnamed: D_↑.2, K_↑.2
unnamed: D_→.2, K_→.2
unnamed: D_↓.2, K_↓.2
unnamed: R21.1, SW1.2, U6.13
unnamed: R22.1, U6.33
unnamed: R23.1, U6.3
unnamed: R24.1, U6.4
unnamed: R23.2, USB6.2
unnamed: R24.2, USB6.3
VCC: C39.1, C40.1, C41.1, C42.1, R21.2, U6.2, U6.14, U6.24, USB6.1

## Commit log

2020-03-21 Add submodules
2020-03-21 Add footprint libraries
2020-03-21 Used the MrKeebs PCB generator to quickly do layout for the pcb
2020-03-25 Added Type-C connector, footprints
2020-03-25 actually added usbc and footprints
2020-03-27 Diode placing in progress
2020-03-28 Ran column traces, debating on whether to have columns on front or back of pcb
2020-04-07 completed routing, removed hotswap, added esd protection
2020-04-12 replaced crytsal with a murata oscillator. tidied up routing, and added filled zones.
2020-04-12 removed unused libraries
2020-04-12 Housekeeping
